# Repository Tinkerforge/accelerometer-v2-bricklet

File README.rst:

Accelerometer Bricklet 2.0
==========================

This repository contains the firmware source code and the hardware design
files. The documentation generator configs can be found at
https://github.com/Tinkerforge/generators

Repository Content
------------------

software/:
 * examples/: Examples for all supported languages
 * build/: Compiled files
 * src/: Source code of firmware
 * Makefile: Makefile to build project

hardware/:
 * Contains KiCad project files and additionally schematics as PDF

datasheets/:
 * Contains datasheets for sensors and complex ICs that are used

Hardware
--------

The hardware is designed with the open source EDA Suite KiCad
(http://www.kicad.org). Before you are able to open the files,
you have to install the Tinkerforge kicad-libraries
(https://github.com/Tinkerforge/kicad-libraries). You can either clone
them directly in hardware/ or clone them in a separate folder and
symlink them into hardware/
(ln -s kicad_path/kicad-libraries project_path/hardware). After that you
can open the .pro file in hardware/ with KiCad and from there view and
modify the schematics and the PCB layout.

Software
--------

If you want to do your own Brick/Bricklet firmware development we highly
recommend that you use our build environment setup script and read the
tutorial (https://www.tinkerforge.com/en/doc/Tutorials/Tutorial_Build_Environment/Tutorial.html).

To compile the C code we recommend you to install the newest GNU Arm Embedded
Toolchain (https://launchpad.net/gcc-arm-embedded/+download).
You also need to install bricklib2 (https://github.com/Tinkerforge/bricklib2).

You can either clone it directly in software/src/ or clone it in a
separate folder and symlink it into software/src/
(ln -s bricklib_path/bricklib2 project_path/software/src/). Finally make sure to
have CMake installed (http://www.cmake.org/cmake/resources/software.html).

After that you can build the firmware by invoking make in software/.
The firmware (.zbin) can then be found in software/build/ and uploaded
with brickv (click button "Flashing" on start screen).

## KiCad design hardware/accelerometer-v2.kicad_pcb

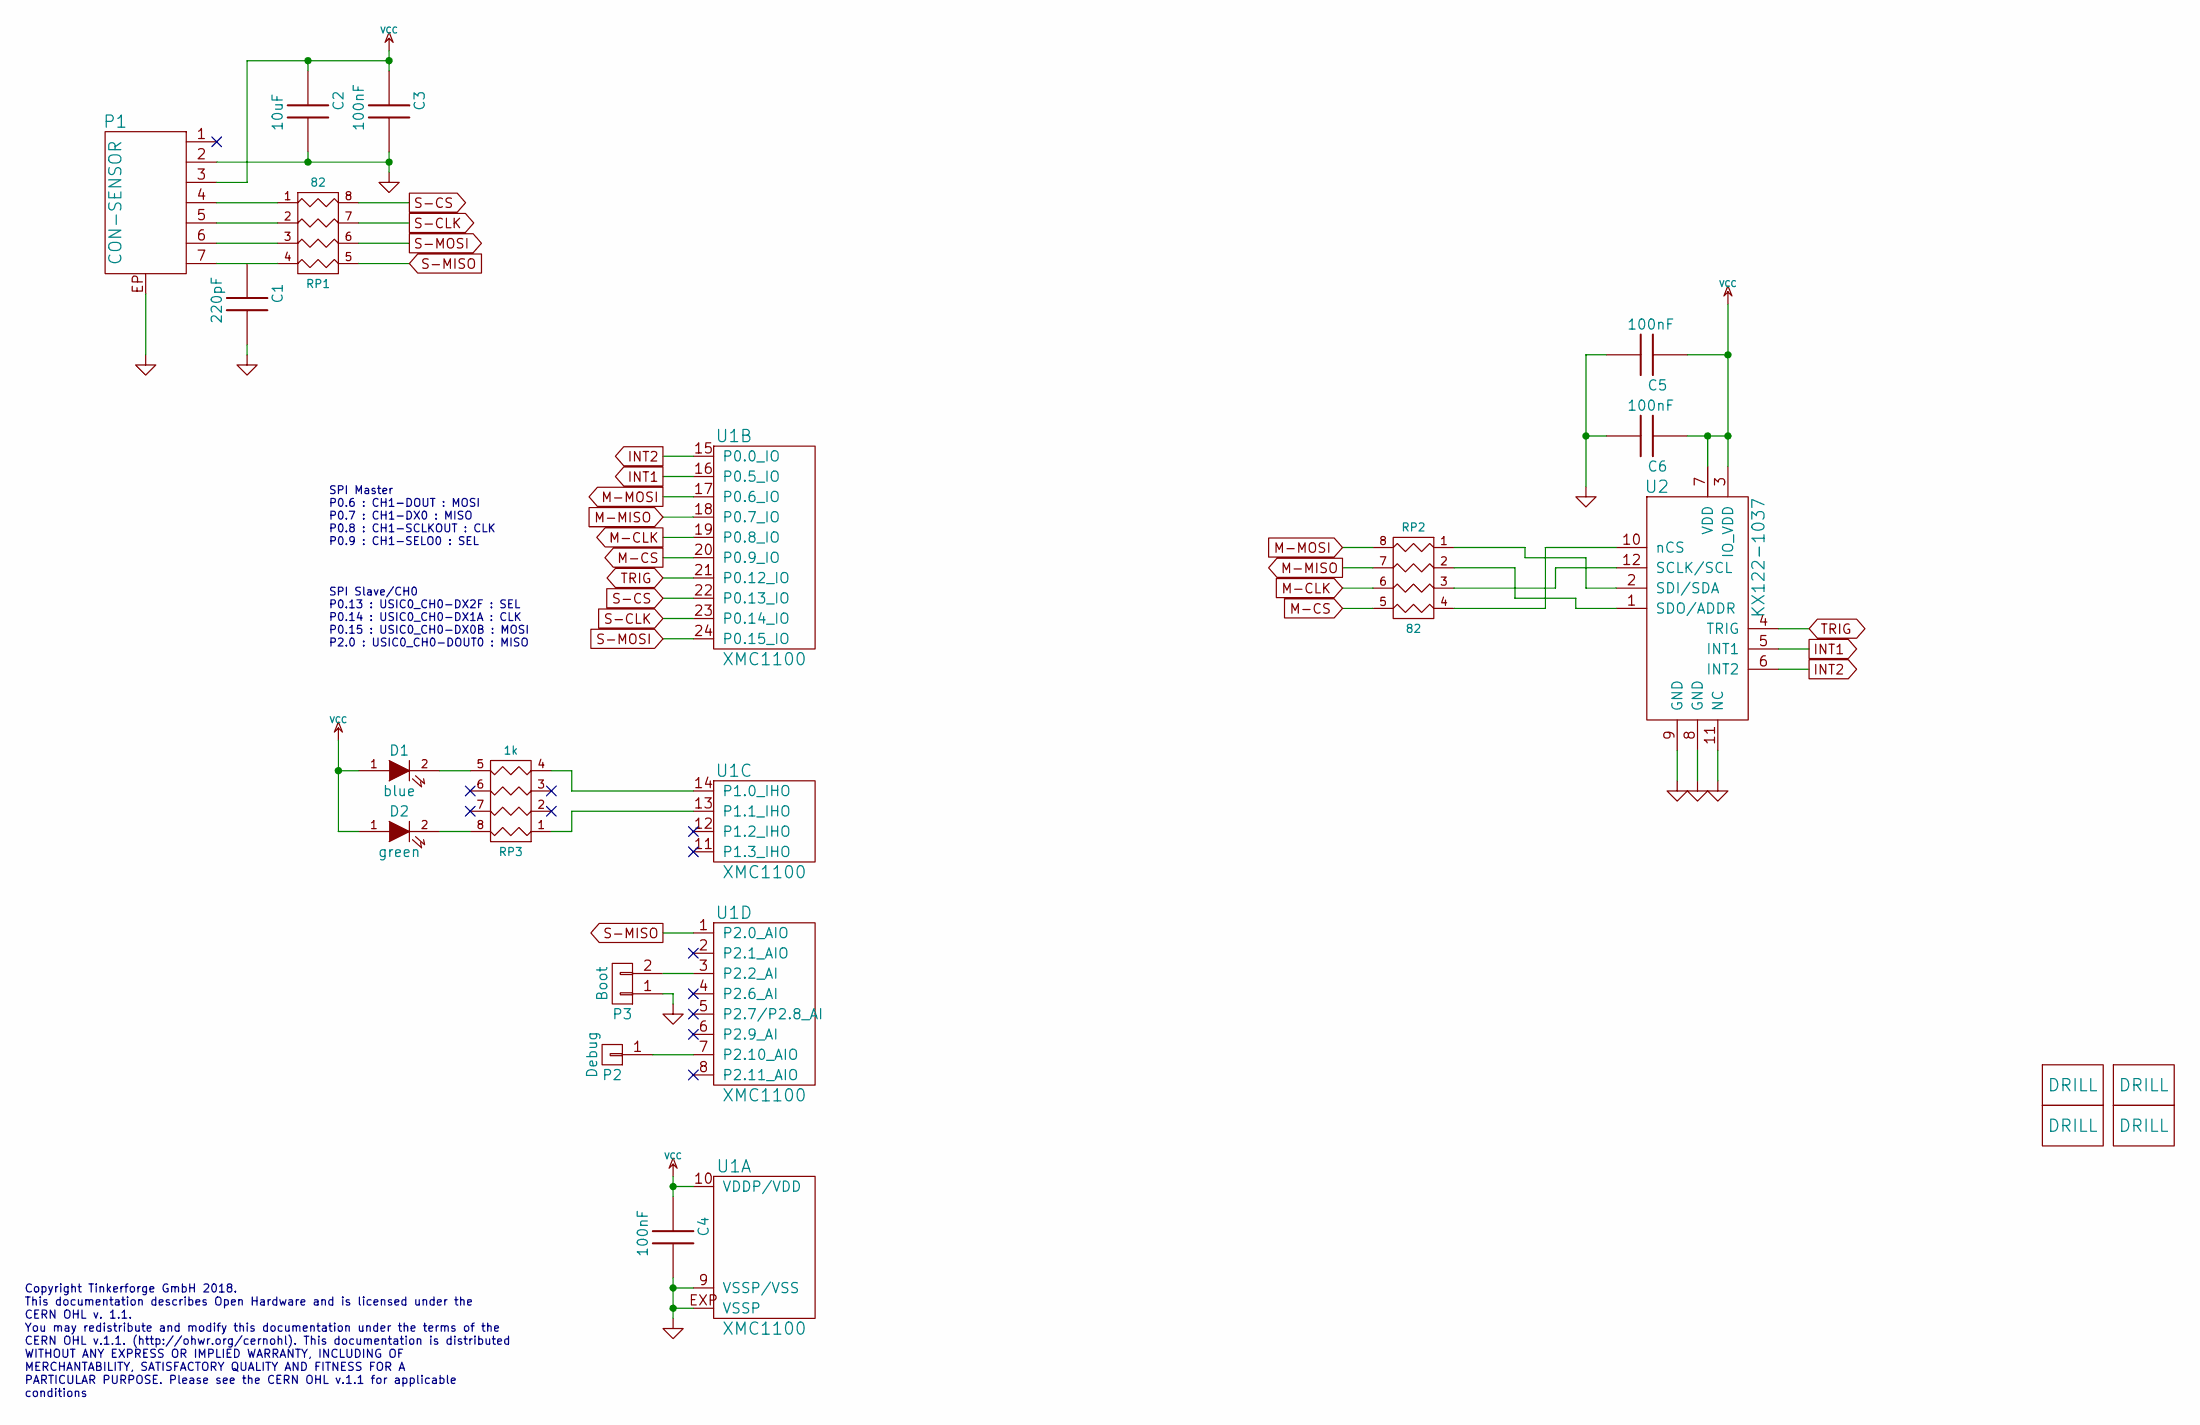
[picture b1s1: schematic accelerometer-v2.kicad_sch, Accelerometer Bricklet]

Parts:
C1: 220pF; C0402F
C2: 10uF; C0805
C3, C4, C5, C6: 100nF; C0603F
D1: blue; D0603F
D2: green; D0603F
P1: CON-SENSOR; CON-SENSOR2
P2: Debug; DEBUG_PAD
P3: Boot; SolderJumper
RP1, RP2: 82; 4X0402
RP3: 1k; 4X0603
U1: XMC1100; QFN24-4x4mm-0.5mm
U2: KX122-1037
U3, U4, U5, U6: DRILL; DRILL_NP

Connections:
GND: C1.2, C2.2, C3.2, C4.2, C5.2, C6.2, P1.2, P1.EP, P3.1, U1.9 (VSSP/VSS), U1.EXP (VSSP), U2.8 (GND), U2.9 (GND), U2.11 (NC)
INT1: U1.16 (P0.5_IO), U2.5 (INT1)
INT2: U1.15 (P0.0_IO), U2.6 (INT2)
M-CLK: RP2.6 (R3), U1.19 (P0.8_IO)
M-CS: RP2.5 (R4), U1.20 (P0.9_IO)
M-MISO: RP2.7 (R2), U1.18 (P0.7_IO)
M-MOSI: RP2.8 (R1), U1.17 (P0.6_IO)
unnamed: D1.2 (K), RP3.5 (R4)
unnamed: D2.2 (K), RP3.8 (R1)
unnamed: P1.4, RP1.1
unnamed: P1.5, RP1.2
unnamed: P1.6, RP1.3
unnamed: P2.1, U1.7 (P2.10_AIO)
unnamed: P3.2, U1.3 (P2.2_AI)
unnamed: RP2.1, U2.2 (SDI/SDA)
unnamed: RP2.2, U2.1 (SDO/ADDR)
unnamed: RP2.3, U2.12 (SCLK/SCL)
unnamed: RP2.4, U2.10 (nCS)
unnamed: RP3.1, U1.13 (P1.1_IHO)
unnamed: RP3.4, U1.14 (P1.0_IHO)
S-CLK: RP1.7 (R2), U1.23 (P0.14_IO)
S-CS: RP1.8 (R1), U1.22 (P0.13_IO)
S-MISO: RP1.5 (R4), U1.1 (P2.0_AIO)
S-MOSI: RP1.6 (R3), U1.24 (P0.15_IO)
TRIG: U1.21 (P0.12_IO), U2.4 (TRIG)
VCC: C2.1, C3.1, C4.1, C5.1, C6.1, D1.1 (A), D2.1 (A), P1.3, U1.10 (VDDP/VDD), U2.3 (IO_VDD), U2.7 (VDD)

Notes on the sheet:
Copyright Tinkerforge GmbH 2018. This documentation describes Open Hardware and is licensed under the CERN OHL v. 1.1. You may redistribute and modify this documentation under the terms of the CERN OHL v.1.1. (http://ohwr.org/cernohl). This documentation is distributed WITHOUT ANY EXPRESS OR IMPLIE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
SPI Master P0.6 : CH1-DOUT : MOSI P0.7 : CH1-DX0 : MISO P0.8 : CH1-SCLKOUT : CLK P0.9 : CH1-SELO0 : SEL
SPI Slave/CH0 P0.13 : USIC0_CH0-DX2F : SEL P0.14 : USIC0_CH0-DX1A : CLK P0.15 : USIC0_CH0-DX0B : MOSI P2.0 : USIC0_CH0-DOUT0 : MISO

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
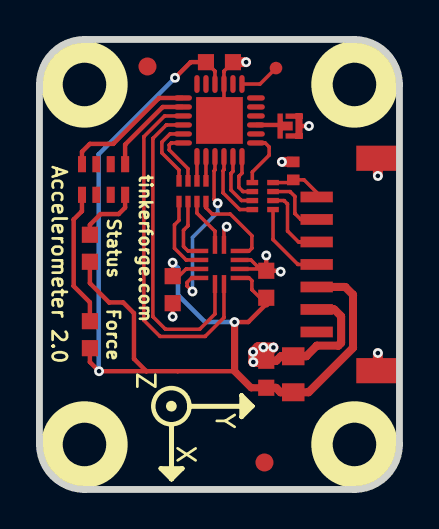
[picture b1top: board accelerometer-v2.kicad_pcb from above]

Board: 2 copper layers, 20.0 x 25.0 mm, 24 parts (2 on the bottom side), 27 nets.

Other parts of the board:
Fiducial_Mark: VAL**; Fiducial_Mark
Fiducial_Mark#2: VAL**; Fiducial_Mark
VAL: WEEE_7mm
VAL#2: CE_5mm

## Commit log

2018-06-22 Add datasheets
2018-06-22 Add schematic
2018-06-22 assign all footprints
2018-06-22 Add layout (tbc)
2018-06-25 Fix some pins
2018-06-25 Add layout
2018-06-25 Minor optical adjustments
2018-06-28 Fix readme
2018-06-28 Add .gitignore
2018-07-04 Fix text
2018-07-11 Fix origin
2018-07-25 Add auto-generated stub firmware
2018-10-24 fix footprint numbering and routing
2018-11-06 change processor xmc1100 -> xmc1302
2018-11-07 Add simple Acceleration/Configuration API and implementation
    This implementation works up to ~800Hz. The KX122 supports data rates
    up to 32kHz, for this we have to introduce an optimized streaming function
2018-11-07 Add missing sym-lib-table file
2018-11-07 Add vscode config directory to .gitignore
2018-11-08 Add continuous acceleration support
    This is currently not working well, data is corrupted in the
    KX122 fifo. We need to read it from register directly...
2018-11-09 change back to xmc1100
2018-11-09 change force led to green
2018-11-09 Read acceleration data from register instead of fifo
    The fifo of the KX122 is not usable, since it does not write new
    data during a read of the fifo. We just poll the acceleration
    registers with the full 25kHz rate instead.
2018-11-09 Remove unused code
2018-11-09 Increase readability of enable adding
2018-11-12 change processor to xmc1302
2018-11-12 Use XMC1300 instead of XMC1100
    At the moment we can fit the firmware in the XMC1100, but we might
    want to add support for double tap and free-fall detection. This would
    probably not fit anymore.
2019-01-25 Rename pdf
2019-01-25 Make sure bootloader fix is enabled
2019-01-28 Turn logging off
2019-01-28 Add initial version rev to changelog
2019-01-29 Change back to XMC1100, there is enough space left
2019-01-29 Resize EEPROM emulation size to 256 Byte
2019-01-29 Add examples.
2019-01-29 specify processor as xmc1100
2019-01-29 fix sym table
2019-01-29 add 3d data
2019-01-29 Remove in-development marker
2019-03-28 mqtt: Fix whitespace.
2019-04-29 Add continuous callback example for MATLAB/Octave
2019-05-29 Increase version for new release (changes in bricklib2)
2019-05-29 Add rev to changelog
2019-07-31 Add support for filter configuration to API
2019-07-31 Add ref for 2.0.2
2019-08-22 c: Adapt to bindings changes
2020-01-13 examples: Use python3 input instead of python2 raw_input.
2020-01-13 examples: mqtt: Remove trailing whitespace.
2020-08-19 Add uc examples.
2020-08-25 uc: Fix whitespace
2020-08-27 uc: Fix warnings.
2020-09-02 uc: Add example driver note.
2020-10-16 uc: Fix divisor type.
2021-10-25 Update KiCad link
    https://www.kicad.org/blog/2021/10/Avoid-links-to-former-kicad-domain/
2022-04-19 examples: uc: Rename TF_HalContext to TF_HAL.
2022-04-27 uc: Adapt to bindings changes
2022-04-27 matlab: Add pitch/roll example
2022-07-06 Add license files.
2024-10-29 fix library settings
2024-10-29 move to new kicad format
2025-10-04 Fix compatibility with new Docker build image (GCC 14.2.1)

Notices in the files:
hardware/accelerometer-v2.kicad_pcb:
Licensed under CERN OHL v.1.1
Copyright (©) 2018, B.Nordmeyer
